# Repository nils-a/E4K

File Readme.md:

# E4K

This is my documentation on adding qmk to my Microsoft Natural Ergonomic Keyboard 4000.

## Steps / Changes

The first step is to remove the old board and reconstruct the matrix of the keys.
I started out by designing a "breakout board" which can be utilized for that task.

Next steps will follow when I have the time.

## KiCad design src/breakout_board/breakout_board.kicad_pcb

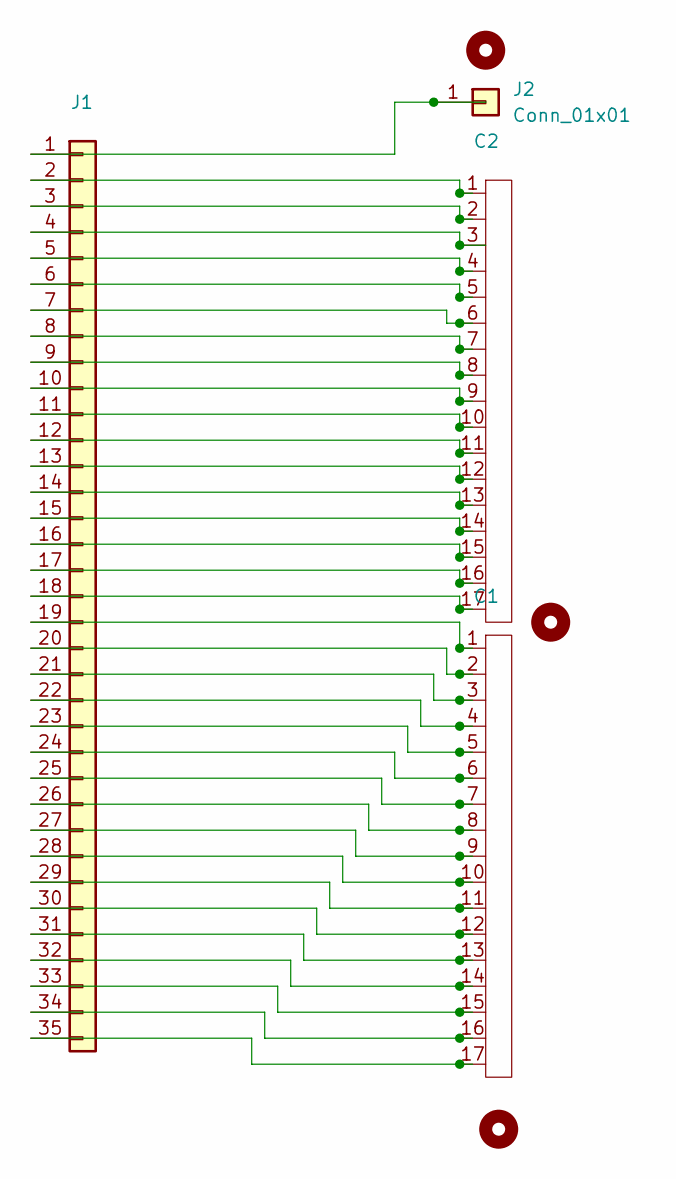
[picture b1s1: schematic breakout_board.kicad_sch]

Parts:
C1, C2: 17pin_solder_pads
H1, H2, H3: MountingHole; MountingHole_5mm
J1: Conn_01x35; PinHeader_1x35_P2.54mm_Vertical
J2: Conn_01x01; gnd_connector

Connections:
unnamed: J1.1, J2.1
unnamed: C2.1, J1.2
unnamed: C2.2, J1.3
unnamed: C2.3, J1.4
unnamed: C2.4, J1.5
unnamed: C2.5, J1.6
unnamed: C2.6, J1.7
unnamed: C2.7, J1.8
unnamed: C2.8, J1.9
unnamed: C2.9, J1.10
unnamed: C2.10, J1.11
unnamed: C2.11, J1.12
unnamed: C2.12, J1.13
unnamed: C2.13, J1.14
unnamed: C2.14, J1.15
unnamed: C2.15, J1.16
unnamed: C2.16, J1.17
unnamed: C2.17, J1.18
unnamed: C1.1, J1.19
unnamed: C1.2, J1.20
unnamed: C1.3, J1.21
unnamed: C1.4, J1.22
unnamed: C1.5, J1.23
unnamed: C1.6, J1.24
unnamed: C1.7, J1.25
unnamed: C1.8, J1.26
unnamed: C1.9, J1.27
unnamed: C1.10, J1.28
unnamed: C1.11, J1.29
unnamed: C1.12, J1.30
unnamed: C1.13, J1.31
unnamed: C1.14, J1.32
unnamed: C1.15, J1.33
unnamed: C1.16, J1.34
unnamed: C1.17, J1.35

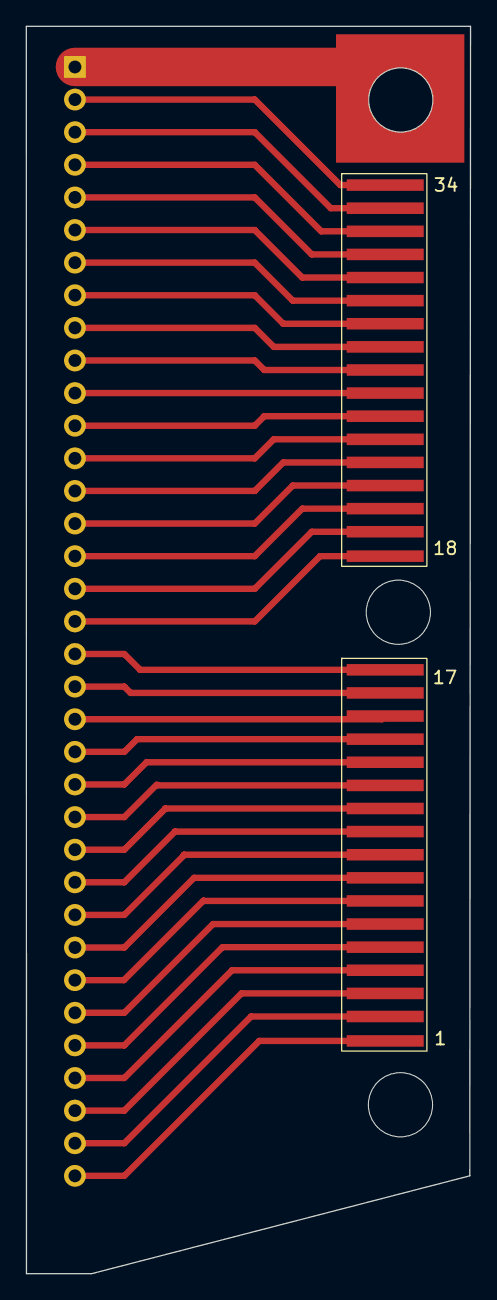
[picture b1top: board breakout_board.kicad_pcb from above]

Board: 2 copper layers, 34.6 x 97.1 mm, 7 parts (1 on the bottom side), 35 nets.

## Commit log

2023-07-29 inital commit
2023-07-31 breakout board
